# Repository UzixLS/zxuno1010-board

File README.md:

## ZX-UNO.1010
10x10cm PCB variant of ZX-Uno project

[[More photos]](images/README.md)

Tech specs:
- Fully compatible with ZX Uno v4.1 and ZX-Uno VGA 2M
- XC6SLX9 FPGA
- 2Mb SRAM memory
- VGA video output
- PAL/NTSC video + audio output via 3.5 jack connector (raspberry-pi compatible pinout)
- PS/2 keyboard and mouse ports
- 2xDB-9 ports for Atari-compatible joysticks
- SD/microSD card slot
- Tape input via Bluetooth module or ordinary 3.5 jack
- MIDI
- WiFi module
- RTC (starting from rev.B)
- Type C (starting from rev.D) or MicroUSB power supply
- Board optimized for G738 and G706 cases

FAQ on official site: [link](https://uto.speccy.org/zxunofaq_en.html)

Some random photos: [link](https://cloud.err200.net/index.php/s/73TR85tYZkMm8Ax?path=%2Fzxuno1010)

### Changelog
* Rev.A - first release ([main pcb errata](pcb/rev.A/ERRATA.txt) and [covers errata](pcb_covers/rev.A/ERRATA.txt)).
* Rev.A1 - fixes all known issues of rev.A.
* Rev.B:
    * added RTC
    * changed second joystick port wiring - in rev.A it's has been wired like in ZXUNO-VGA2M, but now it's wired like Joysplitter, which is officially supported way
    * joysticks are now powered by +5V rail instead of +3.3V - this should improve compatibility with various RF gamepads
    * optimized SAM2695 footprint for hand soldering
    * added opamp for proper MIDI sound mixing
    * added buffer in DAC circuit
    * added separate LDO for SD card and WiFi module
    * added resistor between WiFi's GPIO15 and GND to prevent IC heating
    * remove beeper (which wasn't used anyway)
    * improved power distribution for FPGA chip
    * pcb corners are rounded now
    * experimental tape-in circuit
* Rev.C:
    * added dedicated LDO for audio to improve noise floor
    * added optional capacitor for NTSC quartz stability
    * added missing decoupling capacitor on RTC power rail
    * added current-limiting resistors after opamp on sound output
    * changed R76, R80 from 10kΩ to 8.2kΩ
    * changed U10 opamp from NE5532 to LMV358 as it better suited for low-voltage operation
    * 3mm front leds replaced by 5mm
    * experimental reset circuit based on MAX809
    * reverted to old tape-in circuit
* Rev.D:
    * used USB Type C instead of Micro USB
    * PJ-320 3.5mm jack replaced by PJ-322
    * added solder jumper to select 3.5mm jack CVBS pinout
    * MIDI synthesizer U6 uses clean analog power rail now
    * improved W25Q128 footprint to able to install IC in WSON package
    * some minor PCB layout changes to reduce WiFi interference
    * reverted to old reset circuit
* Rev.D1:
    * changed R16 from 220Ω to 1kΩ to reduce power led bightness
    * changed R70, R71 from 10kΩ to 12kΩ to improve balance with AY
    * changed C51 from 100nF to 1uF to improve audio noise floor
    * changed C13 value as some quartz failed to start with 4.3pF load
    * changed U17 from LP2985-3.3 to TPS7A2033PDBVR due to better PSRR
    * changed U15 from 74LVC2G34 to 74LVC2G04 as it's more common in my projects

### References
* ZX Uno official site: [link](https://zxuno.speccy.org/index_e.shtml)
* ZX Uno VGA 2M: [link](https://github.com/ManuFerHi/ZXUNO_VGA_2M)
* Great collection of cores, games and much stuff for ZX Uno: [link](https://www.zxuno.com/forum/viewtopic.php?f=27&t=4142), [in english](https://www-zxuno-com.translate.goog/forum/viewtopic.php?f=27&t=4142&_x_tr_sl=es&_x_tr_tl=en)

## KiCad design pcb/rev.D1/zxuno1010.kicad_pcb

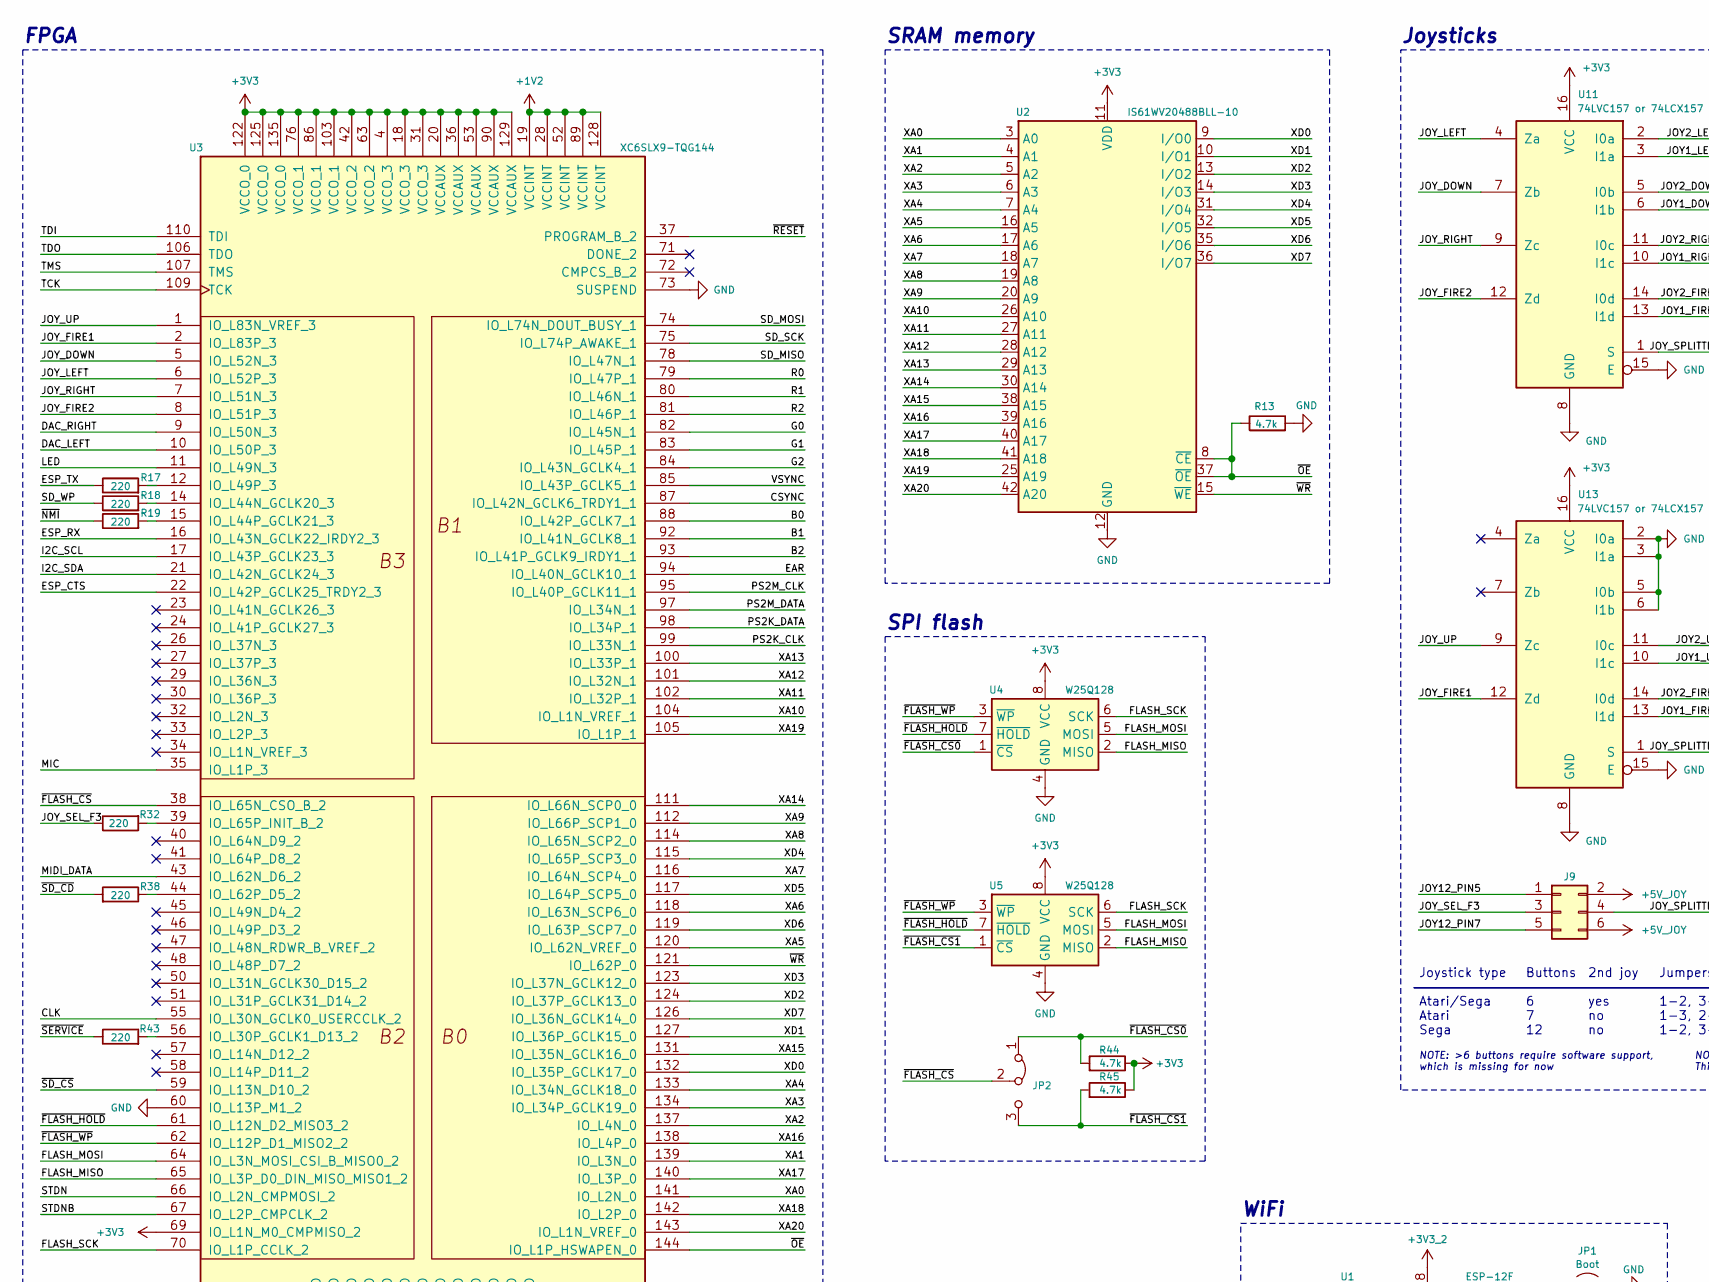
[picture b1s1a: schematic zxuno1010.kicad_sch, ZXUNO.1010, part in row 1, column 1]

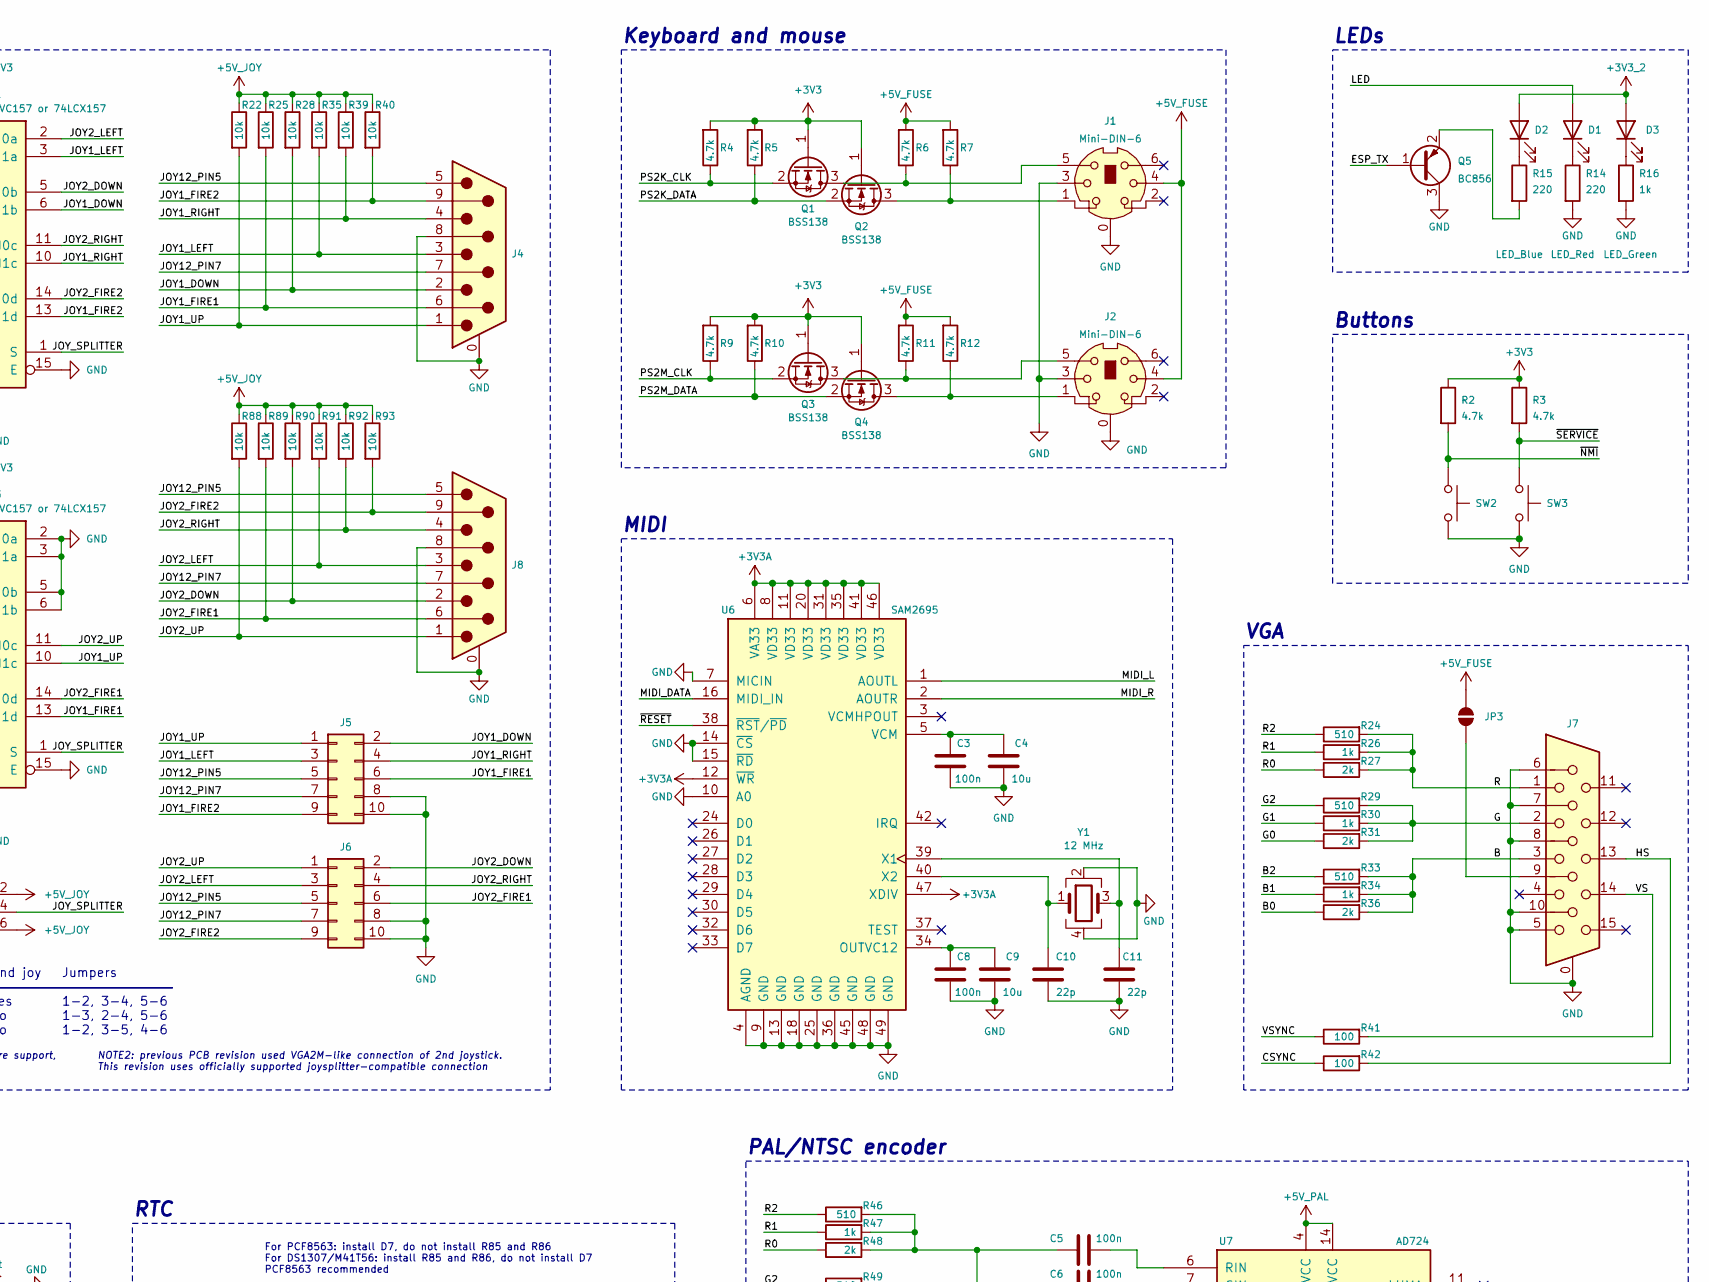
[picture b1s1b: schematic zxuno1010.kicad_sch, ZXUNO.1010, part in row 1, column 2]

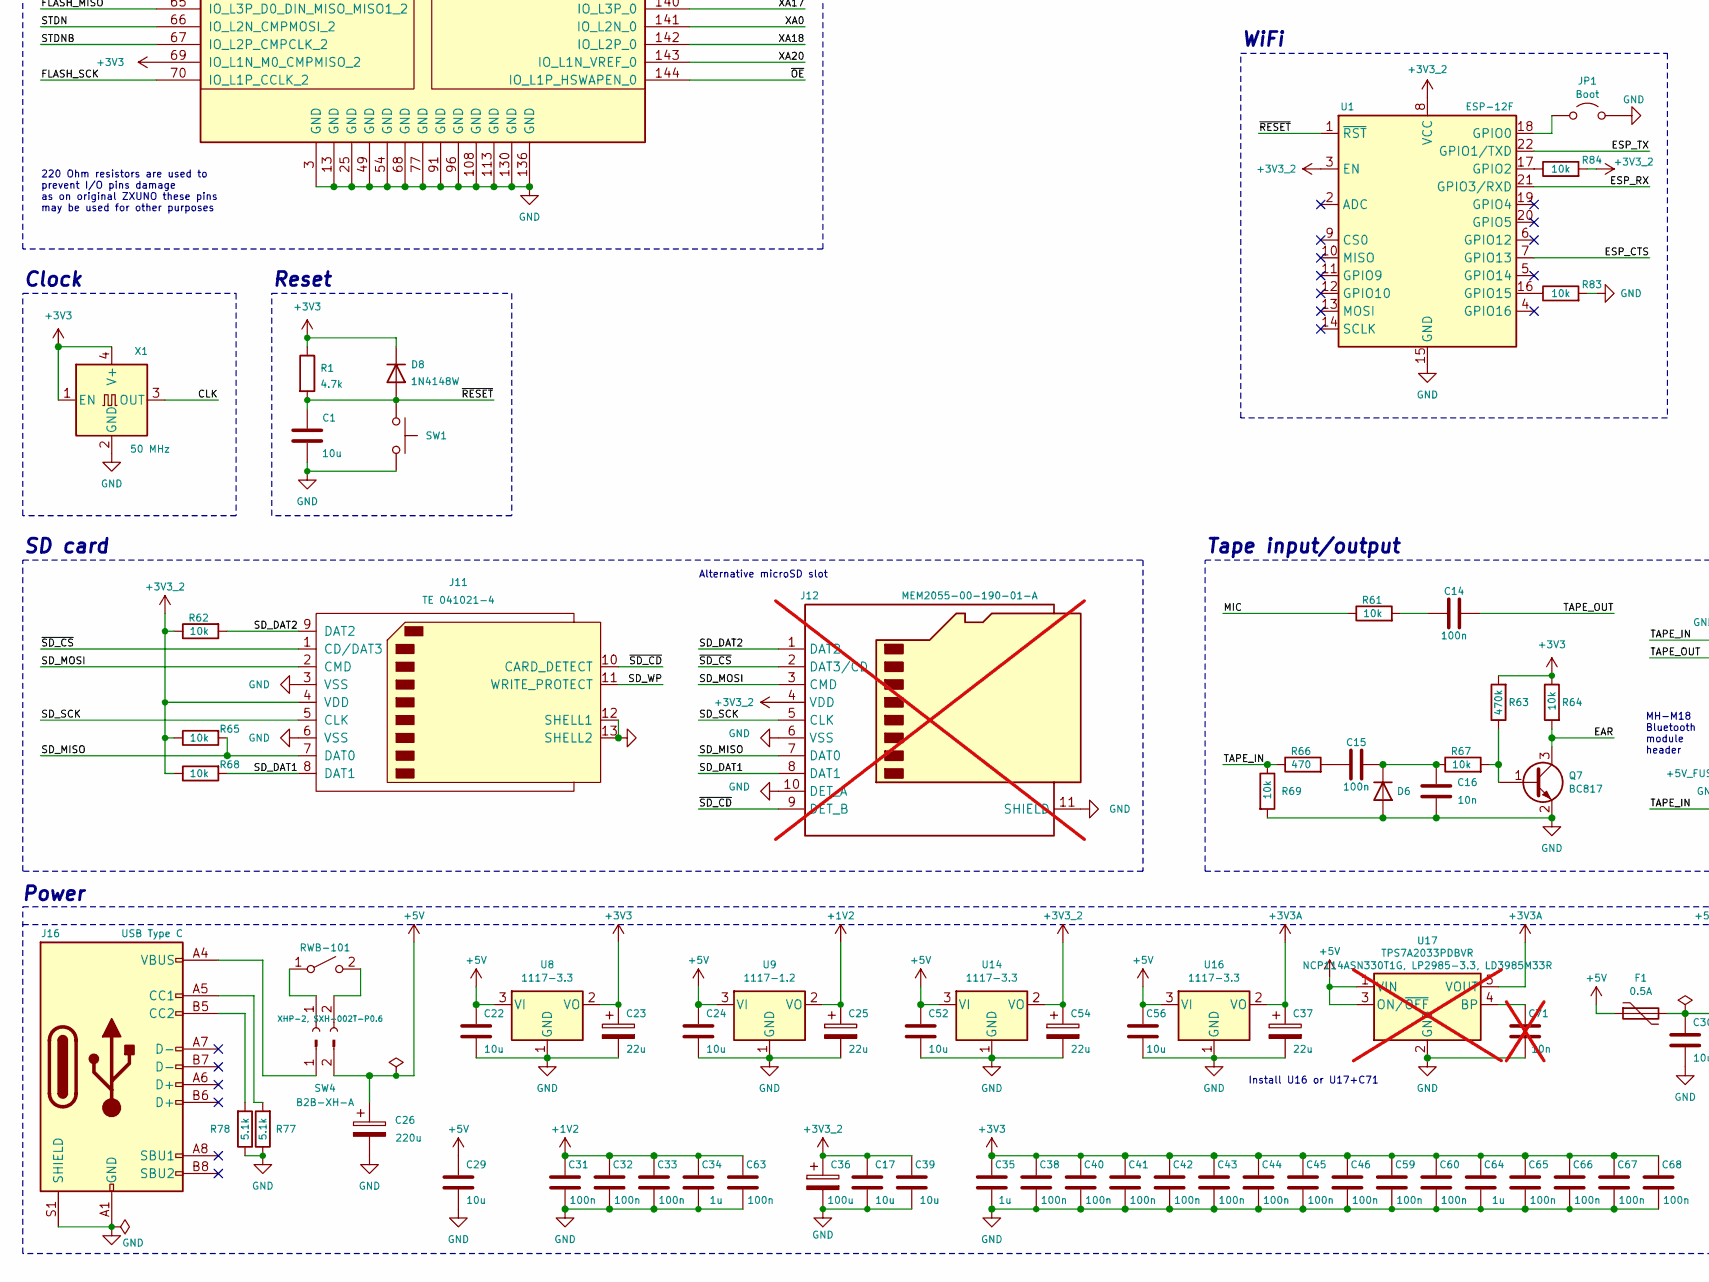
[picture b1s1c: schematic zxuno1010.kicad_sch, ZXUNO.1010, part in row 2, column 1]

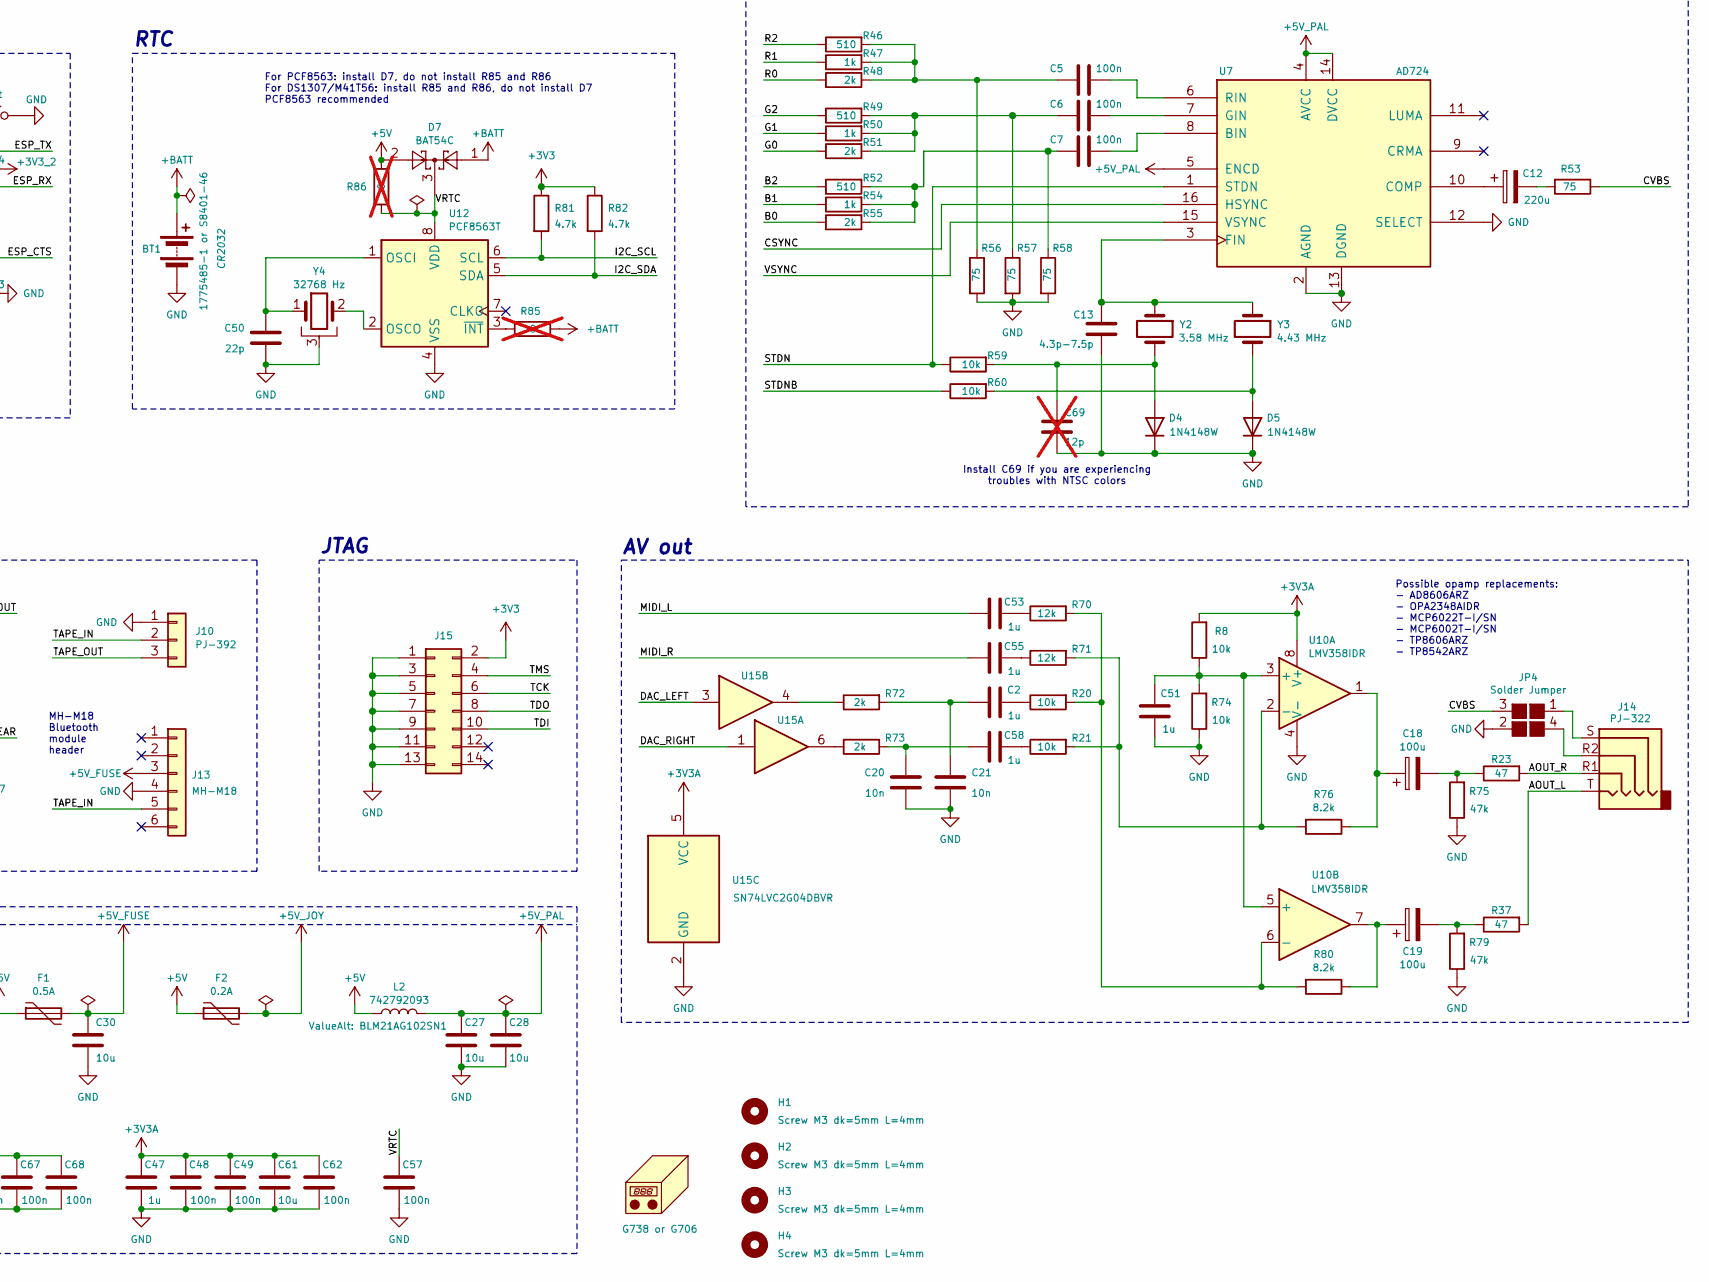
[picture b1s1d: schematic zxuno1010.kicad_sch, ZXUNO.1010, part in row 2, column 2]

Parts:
BT1: 1775485-1 or S8401-46; CR2032V
C1, C4, C9, C17, C22, C24, C27, C28, C29, C30, C39, C52, C56, C61: 10u; C_0805_2012Metric_Pad1.18x1.45mm_HandSolder
C2, C34, C35, C47, C51, C53, C55, C58, C64: 1u; C_0603_1608Metric_Pad1.08x0.95mm_HandSolder
C3, C5, C6, C7, C8, C14, C15, C31, C32, C33, C38, C40, C41, C42, C43, C44, C45, C46, C48, C49, C57, C59, C60, C62, C63, C65, C66, C67, C68: 100n; C_0603_1608Metric_Pad1.08x0.95mm_HandSolder
C10, C11, C50: 22p; C_0603_1608Metric_Pad1.08x0.95mm_HandSolder
C12, C26: 220u; CP_Elec_6.3x7.7
C13: 4.3p-7.5p; C_0603_1608Metric_Pad1.08x0.95mm_HandSolder
C16, C20, C21: 10n; C_0603_1608Metric_Pad1.08x0.95mm_HandSolder
C18, C19, C36: 100u; CP_Elec_5x5.9
C23, C25, C37, C54: 22u; CP_EIA-3216-18_Kemet-A_Pad1.58x1.35mm_HandSolder
C69: 12p; C_0603_1608Metric_Pad1.08x0.95mm_HandSolder; not fitted
C71: 10n; C_0603_1608Metric_Pad1.08x0.95mm_HandSolder; not fitted
D1: LED_Red; LED_D5.0mm_Horizontal_O1.27mm_Z3.0mm
D2: LED_Blue; LED_D5.0mm_Horizontal_O1.27mm_Z3.0mm
D3: LED_Green; LED_D5.0mm_Horizontal_O1.27mm_Z3.0mm
D4, D5, D6, D8: 1N4148W; D_SOD-123
D7: BAT54C; SOT-23
F1: 0.5A; Fuse_1812_4532Metric_Pad1.30x3.40mm_HandSolder
F2: 0.2A; Fuse_1812_4532Metric_Pad1.30x3.40mm_HandSolder
H1, H2, H3, H4: Screw M3 dk=5mm L=4mm; MountingHole_3.2mm_M3_dk5.2mm_Mask
J1, J2: Mini-DIN-6; minidin-6
J3: XHP-2, SXH-002T-P0.6
J4, J8: DB9-M; DSUB-9_Male_Horizontal_P2.77x2.84mm_EdgePinOffset4.94mm_Hou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
J5, J6: Conn_02x05_Odd_Even; PinHeader_2x05_P2.54mm_Vertical
J7: DB15_Female_HighDensity_MountingHoles; DSUB-15-HD_Female_Horizontal_P2.29x1.98mm_EdgePinOffset3.03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
J9: Conn_02x03_Odd_Even; PinHeader_2x03_P2.54mm_Vertical
J10: PJ-392; PinHeader_1x03_P2.54mm_Vertical
J11: TE 041021-4; SD_TE_2041021-mod
J12: MEM2055-00-190-01-A; GCT-MEM2055-00-190-01-A; not fitted
J13: MH-M18; PinHeader_1x06_P2.54mm_Vertical
J14: PJ-322
J15: Conn_02x07_Odd_Even; PinHeader_2x07_P2.54mm_Vertical
J16: USB Type C; USB_C_Receptacle_HRO_TYPE-C-31-M-12_dangling
JP1: Jumper; PinHeader_1x02_P2.54mm_Vertical
JP2: Jumper; PinHeader_1x03_P2.54mm_Vertical
JP3: SolderJumper_2_Open; SolderJumper-2_P1.3mm_Open_RoundedPad1.0x1.5mm
JP4: Solder Jumper; SolderJumper-4_P1.3mm_Open
L2: 742792093; L_0805_2012Metric_Pad1.15x1.40mm_HandSolder
N1: G738 or G706; g738-g706
Q1, Q2, Q3, Q4: BSS138; SOT-23
Q5: BC856; SOT-23
Q7: BC817; SOT-23
R1, R2, R3, R4, R5, R6, R7, R9, R10, R11, R12, R13, R44, R45, R81, R82: 4.7k; R_0603_1608Metric_Pad0.98x0.95mm_HandSolder
R8, R20, R21, R22, R25, R28, R35, R39, R40, R59, R60, R61, R62, R64, R65, R67, R68, R69, R74, R83, R84, R88, R89, R90, R91, R92, R93: 10k; R_0603_1608Metric_Pad0.98x0.95mm_HandSolder
R14, R15, R17, R18, R19, R32, R38, R43: 220; R_0603_1608Metric_Pad0.98x0.95mm_HandSolder
R16, R26, R30, R34, R47, R50, R54: 1k; R_0603_1608Metric_Pad0.98x0.95mm_HandSolder
R23, R37: 47; R_0603_1608Metric_Pad0.98x0.95mm_HandSolder
R24, R29, R33, R46, R49, R52: 510; R_0603_1608Metric_Pad0.98x0.95mm_HandSolder
R27, R31, R36, R48, R51, R55, R72, R73: 2k; R_0603_1608Metric_Pad0.98x0.95mm_HandSolder
R41, R42: 100; R_0603_1608Metric_Pad0.98x0.95mm_HandSolder
R53, R56, R57, R58: 75; R_0603_1608Metric_Pad0.98x0.95mm_HandSolder
R63: 470k; R_0603_1608Metric_Pad0.98x0.95mm_HandSolder
R66: 470; R_0603_1608Metric_Pad0.98x0.95mm_HandSolder
R70, R71: 12k; R_0603_1608Metric_Pad0.98x0.95mm_HandSolder
R75, R79: 47k; R_0603_1608Metric_Pad0.98x0.95mm_HandSolder
R76, R80: 8.2k; R_0603_1608Metric_Pad0.98x0.95mm_HandSolder
R77, R78: 5.1k; R_0603_1608Metric_Pad0.98x0.95mm_HandSolder
R85, R86: 0; R_0603_1608Metric_Pad0.98x0.95mm_HandSolder; not fitted
SW1, SW2, SW3: Push angle button, 6x6x7mm or 6x6x8mm; SW_Tactile_SPST_Angled_PTS645Vx58-2LFS
SW4: B2B-XH-A; JST_XH_B2B-XH-A_1x02_P2.50mm_Vertical
SW5: RWB-101
U1: ESP-12F; ESP-12E
U2: IS61WV20488BLL-10; TSOP-II-44_10.16x18.41mm_P0.8mm
U3: XC6SLX9-TQG144; LQFP-144_20x20mm_P0.5mm
U4, U5: W25Q128; SOIC-8_5.23x5.23mm_P1.27mm-LONG
U6: SAM2695; QFN-48-1EP_6x6mm_P0.4mm_EP4.2x4.2mm
U7: AD724; SOIC-16W_7.5x10.3mm_P1.27mm
U8, U14, U16: 1117-3.3; SOT-223-3_TabPin2
U9: 1117-1.2; SOT-223-3_TabPin2
U10: LMV358IDR; SOIC-8_3.9x4.9mm_P1.27mm
U11, U13: 74LVC157 or 74LCX157; TSSOP-16_4.4x5mm_P0.65mm
U12: PCF8563T; SOIC-8_3.9x4.9mm_P1.27mm
U15: SN74LVC2G04DBVR; SOT-23-6_Handsoldering
U17: TPS7A2033PDBVR; SOT-23-5_HandSoldering; not fitted
X1: 50 MHz; Oscillator_SMD_7050_7.0x5.0mm
Y1: 12 MHz; Crystal_SMD_SeikoEpson_TSX3225-4Pin_3.2x2.5mm_HandSoldering
Y2: 3.58 MHz; Crystal_HC49-4H_Vertical
Y3: 4.43 MHz; Crystal_HC49-4H_Vertical
Y4: 32768 Hz; Crystal_C38-LF_D3.0mm_L8.0mm_Horizontal_1EP_style2

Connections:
+1V2: C25.1, C31.2, C32.2, C33.2, C34.2, C63.2, U3.19 (VCCINT), U3.28 (VCCINT), U3.52 (VCCINT), U3.89 (VCCINT), U3.128 (VCCINT), U9.2 (VO)
+3V3: C23.1, C35.2, C38.2, C40.2, C41.2, C42.2, C43.2, C44.2, C45.2, C46.2, C59.2, C60.2, C64.2, C65.2, C66.2, C67.2, C68.2, D8.1 (K), J15.2, Q1.1 (G), Q2.1 (G), Q3.1 (G), Q4.1 (G), R1.1, R2.1, R3.1, R4.2, R5.2, R9.2, R10.2, R44.1, R45.1, R63.2, R64.1, R81.1, R82.1, U2.11 (VDD), U2.33 (VDD), U3.4 (VCCO_3), U3.18 (VCCO_3), U3.20 (VCCAUX), U3.31 (VCCO_3), U3.36 (VCCAUX), U3.42 (VCCO_2), U3.53 (VCCAUX), U3.63 (VCCO_2), U3.69 (IO_L1N_M0_CMPMISO_2), U3.76 (VCCO_1), U3.86 (VCCO_1), U3.90 (VCCAUX), U3.103 (VCCO_1), U3.122 (VCCO_0), U3.125 (VCCO_0), U3.129 (VCCAUX), U3.135 (VCCO_0), U4.8 (VCC), U5.8 (VCC), U8.2 (VO), U11.16 (VCC), U13.16 (VCC), X1.1 (EN), X1.4 (V+)
+3V3A: C37.1, C47.2, C48.2, C49.2, C61.2, C62.2, R8.2, U6.6 (VA33), U6.8 (VD33), U6.11 (VD33), U6.12 (~WR), U6.20 (VD33), U6.31 (VD33), U6.35 (VD33), U6.41 (VD33), U6.46 (VD33), U6.47 (XDIV), U10.8 (V+), U15.5 (VCC), U16.2 (VO), U17.5 (VOUT)
+3V3_2: C17.2, C36.1, C39.2, C54.1, D2.2 (A), D3.2 (A), J11.4 (VDD), J12.4 (VDD), R62.1, R65.1, R68.1, R84.2, U1.3 (EN), U1.8 (VCC), U14.2 (VO)
+5V: C22.2, C24.2, C26.1, C29.2, C52.2, C56.2, D7.2, F1.1, F2.1, L2.1, R86.2, SW4.2, U8.3 (VI), U9.3 (VI), U14.3 (VI), U16.3 (VI), U17.1 (VIN), U17.3 (ON/~OFF)
+5V_FUSE: C30.2, F1.2, J1.4, J2.4, J13.3, JP3.2 (B), R6.2, R7.2, R11.2, R12.2
+5V_JOY: F2.2, J9.2, J9.6, R22.1, R25.1, R28.1, R35.1, R39.1, R40.1, R88.1, R89.1, R90.1, R91.1, R92.1, R93.1
+5V_PAL: C27.2, C28.2, L2.2, U7.4 (AVCC), U7.5 (ENCD), U7.14 (DVCC)
+BATT: BT1.1 (+), D7.1, R85.2
/AOUT_L: J14.T, R37.2
/AOUT_R: J14.R1, R23.2
/B: J7.3, R33.2, R34.2, R36.2
/B0: R36.1, R55.1, U3.88 (IO_L42P_GCLK7_1)
/B1: R34.1, R54.1, U3.92 (IO_L41N_GCLK8_1)
/B2: R33.1, R52.1, U3.93 (IO_L41P_GCLK9_IRDY1_1)
/CLK: U3.55 (IO_L30N_GCLK0_USERCCLK_2), X1.3 (OUT)
/CSYNC: R42.1, U3.87 (IO_L42N_GCLK6_TRDY1_1), U7.16 (HSYNC)
/CVBS: JP4.3, R53.1
/DAC_LEFT: U3.10 (IO_L50P_3), U15.3
/DAC_RIGHT: U3.9 (IO_L50N_3), U15.1
/EAR: Q7.3 (C), R64.2, U3.94 (IO_L40N_GCLK10_1)
/ESP_CTS: U1.7 (GPIO13), U3.22 (IO_L42P_GCLK25_TRDY2_3)
/ESP_RX: U1.21 (GPIO3/RXD), U3.16 (IO_L43N_GCLK22_IRDY2_3)
/ESP_TX: Q5.1 (B), R17.1, U1.22 (GPIO1/TXD)
/FLASH_MISO: U3.65 (IO_L3P_D0_DIN_MISO_MISO1_2), U4.2 (MISO), U5.2 (MISO)
/FLASH_MOSI: U3.64 (IO_L3N_MOSI_CSI_B_MISO0_2), U4.5 (MOSI), U5.5 (MOSI)
/FLASH_SCK: U3.70 (IO_L1P_CCLK_2), U4.6 (SCK), U5.6 (SCK)
/G: J7.2, R29.2, R30.2, R31.2
/G0: R31.1, R51.1, U3.82 (IO_L45N_1)
/G1: R30.1, R50.1, U3.83 (IO_L45P_1)
/G2: R29.1, R49.1, U3.84 (IO_L43N_GCLK4_1)
/HS: J7.13, R42.2
/I2C_SCL: R81.2, U3.17 (IO_L43P_GCLK23_3), U12.6 (SCL)
/I2C_SDA: R82.2, U3.21 (IO_L42N_GCLK24_3), U12.5 (SDA)
/JOY1_DOWN: J4.2, J5.2, R28.2, U11.6 (I1b)
/JOY1_FIRE1: J4.6, J5.6, R25.2, U13.13 (I1d)
/JOY1_FIRE2: J4.9, J5.9, R40.2, U11.13 (I1d)
/JOY1_LEFT: J4.3, J5.3, R35.2, U11.3 (I1a)
/JOY1_RIGHT: J4.4, J5.4, R39.2, U11.10 (I1c)
/JOY1_UP: J4.1, J5.1, R22.2, U13.10 (I1c)
/JOY2_DOWN: J6.2, J8.2, R90.2, U11.5 (I0b)
/JOY2_FIRE1: J6.6, J8.6, R89.2, U13.14 (I0d)
/JOY2_FIRE2: J6.9, J8.9, R93.2, U11.14 (I0d)
/JOY2_LEFT: J6.3, J8.3, R91.2, U11.2 (I0a)
/JOY2_RIGHT: J6.4, J8.4, R92.2, U11.11 (I0c)
/JOY2_UP: J6.1, J8.1, R88.2, U13.11 (I0c)
/JOY12_PIN5: J4.5, J5.5, J6.5, J8.5, J9.1
/JOY12_PIN7: J4.7, J5.7, J6.7, J8.7, J9.5
/JOY_DOWN: U3.5 (IO_L52N_3), U11.7 (Zb)
/JOY_FIRE1: U3.2 (IO_L83P_3), U13.12 (Zd)
/JOY_FIRE2: U3.8 (IO_L51P_3), U11.12 (Zd)
/JOY_LEFT: U3.6 (IO_L52P_3), U11.4 (Za)
/JOY_RIGHT: U3.7 (IO_L51N_3), U11.9 (Zc)
/JOY_SEL_F3: J9.3, R32.1
/JOY_SPLITTER: J9.4, U11.1 (S), U13.1 (S)
/JOY_UP: U3.1 (IO_L83N_VREF_3), U13.9 (Zc)
/LED: D1.2 (A), U3.11 (IO_L49N_3)
/MIC: R61.1, U3.35 (IO_L1P_3)
/MIDI_DATA: U3.43 (IO_L62N_D6_2), U6.16 (MIDI_IN)
/MIDI_L: C53.1, U6.1 (AOUTL)
/MIDI_R: C55.1, U6.2 (AOUTR)
/PS2K_CLK: Q1.2 (S), R4.1, U3.99 (IO_L33N_1)
/PS2K_DATA: Q2.2 (S), R5.1, U3.98 (IO_L34P_1)
/PS2M_CLK: Q3.2 (S), R9.1, U3.95 (IO_L40P_GCLK11_1)
/PS2M_DATA: Q4.2 (S), R10.1, U3.97 (IO_L34N_1)
/R: J7.1, R24.2, R26.2, R27.2
/R0: R27.1, R48.1, U3.79 (IO_L47P_1)
/R1: R26.1, R47.1, U3.80 (IO_L46N_1)
/R2: R24.1, R46.1, U3.81 (IO_L46P_1)
/SD_DAT1: J11.8 (DAT1), J12.8 (DAT1), R68.2
/SD_DAT2: J11.9 (DAT2), J12.1 (DAT2), R62.2
/SD_MISO: J11.7 (DAT0), J12.7 (DAT0), R65.2, U3.78 (IO_L47N_1)
/SD_MOSI: J11.2 (CMD), J12.3 (CMD), U3.74 (IO_L74N_DOUT_BUSY_1)
/SD_SCK: J11.5 (CLK), J12.5 (CLK), U3.75 (IO_L74P_AWAKE_1)
/SD_WP: J11.11 (WRITE_PROTECT), R18.1
/STDN: R59.1, U3.66 (IO_L2N_CMPMOSI_2), U7.1 (STDN)
/STDNB: R60.1, U3.67 (IO_L2P_CMPCLK_2)
/TAPE_IN: J10.2, J13.5, R66.1, R69.1
/TAPE_OUT: C14.1, J10.3
/TCK: J15.6, U3.109 (TCK)
/TDI: J15.10, U3.110 (TDI)
/TDO: J15.8, U3.106 (TDO)
/TMS: J15.4, U3.107 (TMS)
/VRTC: C57.2, D7.3, R86.1, U12.8 (VDD)
/VS: J7.14, R41.2
/VSYNC: R41.1, U3.85 (IO_L43P_GCLK5_1), U7.15 (VSYNC)
/XA0: U2.3 (A0), U3.141 (IO_L2N_0)
/XA1: U2.4 (A1), U3.139 (IO_L3N_0)
/XA2: U2.5 (A2), U3.137 (IO_L4N_0)
/XA3: U2.6 (A3), U3.134 (IO_L34P_GCLK19_0)
/XA4: U2.7 (A4), U3.133 (IO_L34N_GCLK18_0)
/XA5: U2.16 (A5), U3.120 (IO_L62N_VREF_0)
/XA6: U2.17 (A6), U3.118 (IO_L63N_SCP6_0)
/XA7: U2.18 (A7), U3.116 (IO_L64N_SCP4_0)
/XA8: U2.19 (A8), U3.114 (IO_L65N_SCP2_0)
/XA9: U2.20 (A9), U3.112 (IO_L66P_SCP1_0)
/XA10: U2.26 (A10), U3.104 (IO_L1N_VREF_1)
/XA11: U2.27 (A11), U3.102 (IO_L32P_1)
/XA12: U2.28 (A12), U3.101 (IO_L32N_1)
/XA13: U2.29 (A13), U3.100 (IO_L33P_1)
/XA14: U2.30 (A14), U3.111 (IO_L66N_SCP0_0)
/XA15: U2.38 (A15), U3.131 (IO_L35N_GCLK16_0)
/XA16: U2.39 (A16), U3.138 (IO_L4P_0)
/XA17: U2.40 (A17), U3.140 (IO_L3P_0)
/XA18: U2.41 (A18), U3.142 (IO_L2P_0)
/XA19: U2.25 (A19), U3.105 (IO_L1P_1)
/XA20: U2.42 (A20), U3.143 (IO_L1N_VREF_0)
/XD0: U2.9 (I/O0), U3.132 (IO_L35P_GCLK17_0)
/XD1: U2.10 (I/O1), U3.127 (IO_L36P_GCLK15_0)
/XD2: U2.13 (I/O2), U3.124 (IO_L37P_GCLK13_0)
/XD3: U2.14 (I/O3), U3.123 (IO_L37N_GCLK12_0)
/XD4: U2.31 (I/O4), U3.115 (IO_L65P_SCP3_0)
/XD5: U2.32 (I/O5), U3.117 (IO_L64P_SCP5_0)
/XD6: U2.35 (I/O6), U3.119 (IO_L63P_SCP7_0)
/XD7: U2.36 (I/O7), U3.126 (IO_L36N_GCLK14_0)
/~FLASH_CS0: JP2.1 (A), R44.2, U4.1 (~CS)
/~FLASH_CS1: JP2.3 (B), R45.2, U5.1 (~CS)
/~FLASH_CS: JP2.2 (C), U3.38 (IO_L65N_CSO_B_2)
/~FLASH_HOLD: U3.61 (IO_L12N_D2_MISO3_2), U4.7 (~HOLD), U5.7 (~HOLD)
/~FLASH_WP: U3.62 (IO_L12P_D1_MISO2_2), U4.3 (~WP), U5.3 (~WP)
/~NMI: R2.2, R19.1, SW2.1
/~OE: R13.1, U2.8 (~CE), U2.37 (~OE), U3.144 (IO_L1P_HSWAPEN_0)
/~RESET: C1.2, D8.2 (A), R1.2, SW1.1, U1.1 (~RST), U3.37 (PROGRAM_B_2), U6.38 (~RST/~PD)
/~SD_CD: J11.10 (CARD_DETECT), J12.9 (DET_B), R38.2
/~SD_CS: J11.1 (CD/DAT3), J12.2 (DAT3/CD), U3.59 (IO_L13N_D10_2)
/~SERVICE: R3.2, R43.1, SW3.1
/~WR: U2.15 (~WE), U3.121 (IO_L62P_0)
GND: BT1.2 (-), C1.1, C3.1, C4.1, C8.1, C9.1, C10.1, C11.1, C13.2, C16.2, C17.1, C20.2, C21.2, C22.1, C23.2, C24.1, C25.2, C26.2, C27.1, C28.1, C29.1, C30.1, C31.1, C32.1, C33.1, C34.1, C35.1, C36.2, C37.2, C38.1, C39.1, C40.1, C41.1, C42.1, C43.1, C44.1, C45.1, C46.1, C47.1, C48.1, C49.1, C50.2, C51.1, C52.1, C54.2, C56.1, C57.1, C59.1, C60.1, C61.1, C62.1, C63.1, C64.1, C65.1, C66.1, C67.1, C68.1, C69.2, C71.1, D4.1 (K), D5.1 (K), D6.2 (A), J1.0, J1.3, J2.0, J2.3, J4.0 (PAD), J4.8, J5.8, J5.10, J6.8, J6.10, J7.0, J7.5, J7.6, J7.7, J7.8, J7.10, J8.0 (PAD), J8.8, J10.1, J11.3 (VSS), J11.6 (VSS), J11.12 (SHELL1), J11.13 (SHELL2), J12.6 (VSS), J12.10 (DET_A), J12.11 (SHIELD), J13.4, J15.1, J15.3, J15.5, J15.7, J15.9, J15.11, J15.13, J16.A1 (GND), J16.A12 (GND), J16.B1 (GND), J16.B12 (GND), J16.S1 (SHIELD), JP1.1 (A), JP4.2, Q5.3 (C), Q7.2 (E), R13.2, R14.2, R16.2, R56.2, R57.2, R58.2, R69.2, R74.1, R75.1, R77.1, R78.1, R79.1, R83.2, SW1.2, SW2.2, SW3.2, U1.15 (GND), U2.12 (GND), U2.34 (GND), U3.3 (GND), U3.13 (GND), U3.25 (GND), U3.49 (GND), U3.54 (GND), U3.60 (IO_L13P_M1_2), U3.68 (GND), U3.73 (SUSPEND), U3.77 (GND), U3.91 (GND), U3.96 (GND), U3.108 (GND), U3.113 (GND), U3.130 (GND), U3.136 (GND), U4.4 (GND), U5.4 (GND), U6.4 (AGND), U6.7 (MICIN), U6.9 (GND), U6.10 (A0), U6.13 (GND), U6.14 (~CS), U6.15 (~RD), U6.18 (GND), U6.25 (GND), U6.36 (GND), U6.45 (GND), U6.48 (GND), U6.49 (GND), U7.2 (AGND), U7.12 (SELECT), U7.13 (DGND), U8.1 (GND), U9.1 (GND), U10.4 (V-), U11.8 (GND), U11.15 (E), U12.4 (VSS), U13.2 (I0a), U13.3 (I1a), U13.5 (I0b), U13.6 (I1b), U13.8 (GND), U13.15 (E), U14.1 (GND), U15.2 (GND), U16.1 (GND), U17.2 (GND), X1.2 (GND), Y1.2, Y1.4, Y4.3
unnamed: C2.1, C21.1, R72.2
unnamed: C2.2, R20.1
unnamed: C5.2, R46.2, R47.2, R48.2, R56.1
unnamed: C6.2, R49.2, R50.2, R51.2, R57.1
unnamed: C7.2, R52.2, R54.2, R55.2, R58.1
unnamed: C12.2, R53.2
unnamed: C14.2, R61.2
unnamed: C15.2, R66.2
unnamed: C18.1, R76.1, U10.1
unnamed: C18.2, R23.1, R75.2
unnamed: C19.1, R80.1, U10.7
unnamed: C19.2, R37.1, R79.2
unnamed: C20.1, C58.1, R73.2
unnamed: C53.2, R70.1
unnamed: C55.2, R71.1
unnamed: C58.2, R21.1
unnamed: D1.1 (K), R14.1
unnamed: D2.1 (K), R15.1
unnamed: D3.1 (K), R16.1
unnamed: C69.1, D4.2 (A), R59.2, Y2.2
unnamed: D5.2 (A), R60.2, Y3.2
unnamed: C15.1, C16.1, D6.1 (K), R67.1
unnamed: J3.1, SW5.1 (A)
unnamed: J3.2, SW5.2 (B)
unnamed: J14.R2, JP4.4
unnamed: J16.A5 (CC1), R77.2
unnamed: J16.B5 (CC2), R78.2
unnamed: JP1.2 (B), U1.18 (GPIO0)
unnamed: J7.9, JP3.1 (A)
unnamed: J14.S, JP4.1 (A)
unnamed: J1.5, Q1.3 (D), R6.1
unnamed: J1.1, Q2.3 (D), R7.1
unnamed: J2.5, Q3.3 (D), R11.1
unnamed: J2.1, Q4.3 (D), R12.1
unnamed: Q5.2 (E), R15.2
unnamed: Q7.1 (B), R63.1, R67.2
unnamed: R72.1, U15.4
unnamed: R73.1, U15.6
unnamed: J16.A4 (VBUS), J16.A9 (VBUS), J16.B4 (VBUS), J16.B9 (VBUS), SW4.1
unnamed: R84.1, U1.17 (GPIO2)
unnamed: R83.1, U1.16 (GPIO15)
unnamed: R43.2, U3.56 (IO_L30P_GCLK1_D13_2)
unnamed: R18.2, U3.14 (IO_L44N_GCLK20_3)
unnamed: R19.2, U3.15 (IO_L44P_GCLK21_3)
unnamed: R17.2, U3.12 (IO_L49P_3)
unnamed: R38.1, U3.44 (IO_L62P_D5_2)
unnamed: R32.2, U3.39 (IO_L65P_INIT_B_2)
unnamed: C8.2, C9.2, U6.34 (OUTVC12)
unnamed: C3.2, C4.2, U6.5 (VCM)
unnamed: C11.2, U6.39 (X1), Y1.3
unnamed: C10.2, U6.40 (X2), Y1.1
unnamed: C7.1, U7.8 (BIN)
unnamed: C12.1, U7.10 (COMP)
unnamed: C13.1, U7.3 (FIN), Y2.1, Y3.1
unnamed: C6.1, U7.7 (GIN)
unnamed: C5.1, U7.6 (RIN)
unnamed: C51.2, R8.1, R74.2, U10.3 (+), U10.5 (+)
unnamed: R21.2, R71.2, R76.2, U10.2 (-)
unnamed: R20.2, R70.2, R80.2, U10.6 (-)
unnamed: C50.1, U12.1 (OSCI), Y4.1
unnamed: U12.2 (OSCO), Y4.2
unnamed: R85.1, U12.3 (~INT)
unnamed: C71.2, U17.4 (BP)

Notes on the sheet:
220 Ohm resistors are used to prevent I/O pins damage as on original ZXUNO these pins may be used for other purposes
Reset
Keyboard and mouse
Install C69 if you are experiencing troubles with NTSC colors
JTAG
For PCF8563: install D7, do not install R85 and R86 For DS1307/M41T56: install R85 and R86, do not install D7 PCF8563 recommended
Buttons
LEDs
MIDI
Jumpers 1-2, 3-4, 5-6 1-3, 2-4, 5-6 1-2, 3-5, 4-6
Install U16 or U17+C71
SD card
VGA
2nd joy yes no no
Clock
Tape input/output
NOTE: >6 buttons require software support, which is missing for now
NOTE2: previous PCB revision used VGA2M-like connection of 2nd joystick. This revision uses officially supported joysplitter-compatible connection
SRAM memory
AV out
Buttons 6 7 12
Possible opamp replacements: - AD8606ARZ - OPA2348AIDR - MCP6022T-I/SN - MCP6002T-I/SN - TP8606ARZ - TP8542ARZ
Joysticks
PAL/NTSC encoder
RTC
Alternative microSD slot
Joystick type Atari/Sega Atari Sega
Power
WiFi
FPGA
MH-M18 Bluetooth module header
SPI flash

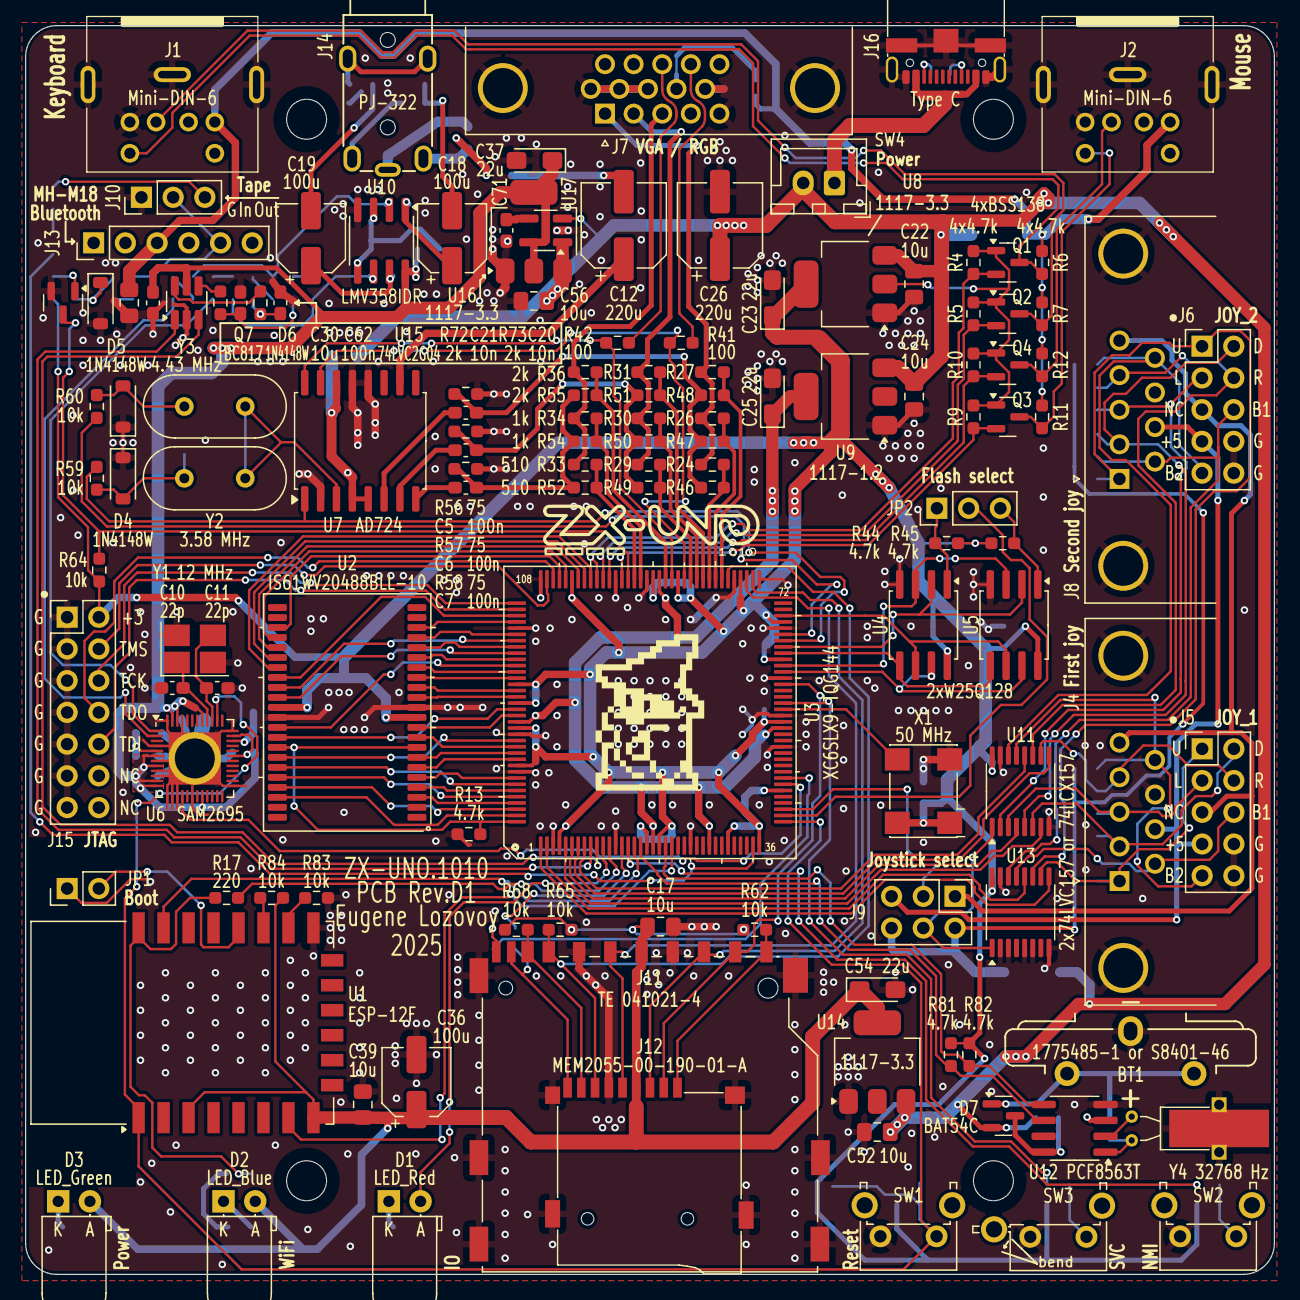
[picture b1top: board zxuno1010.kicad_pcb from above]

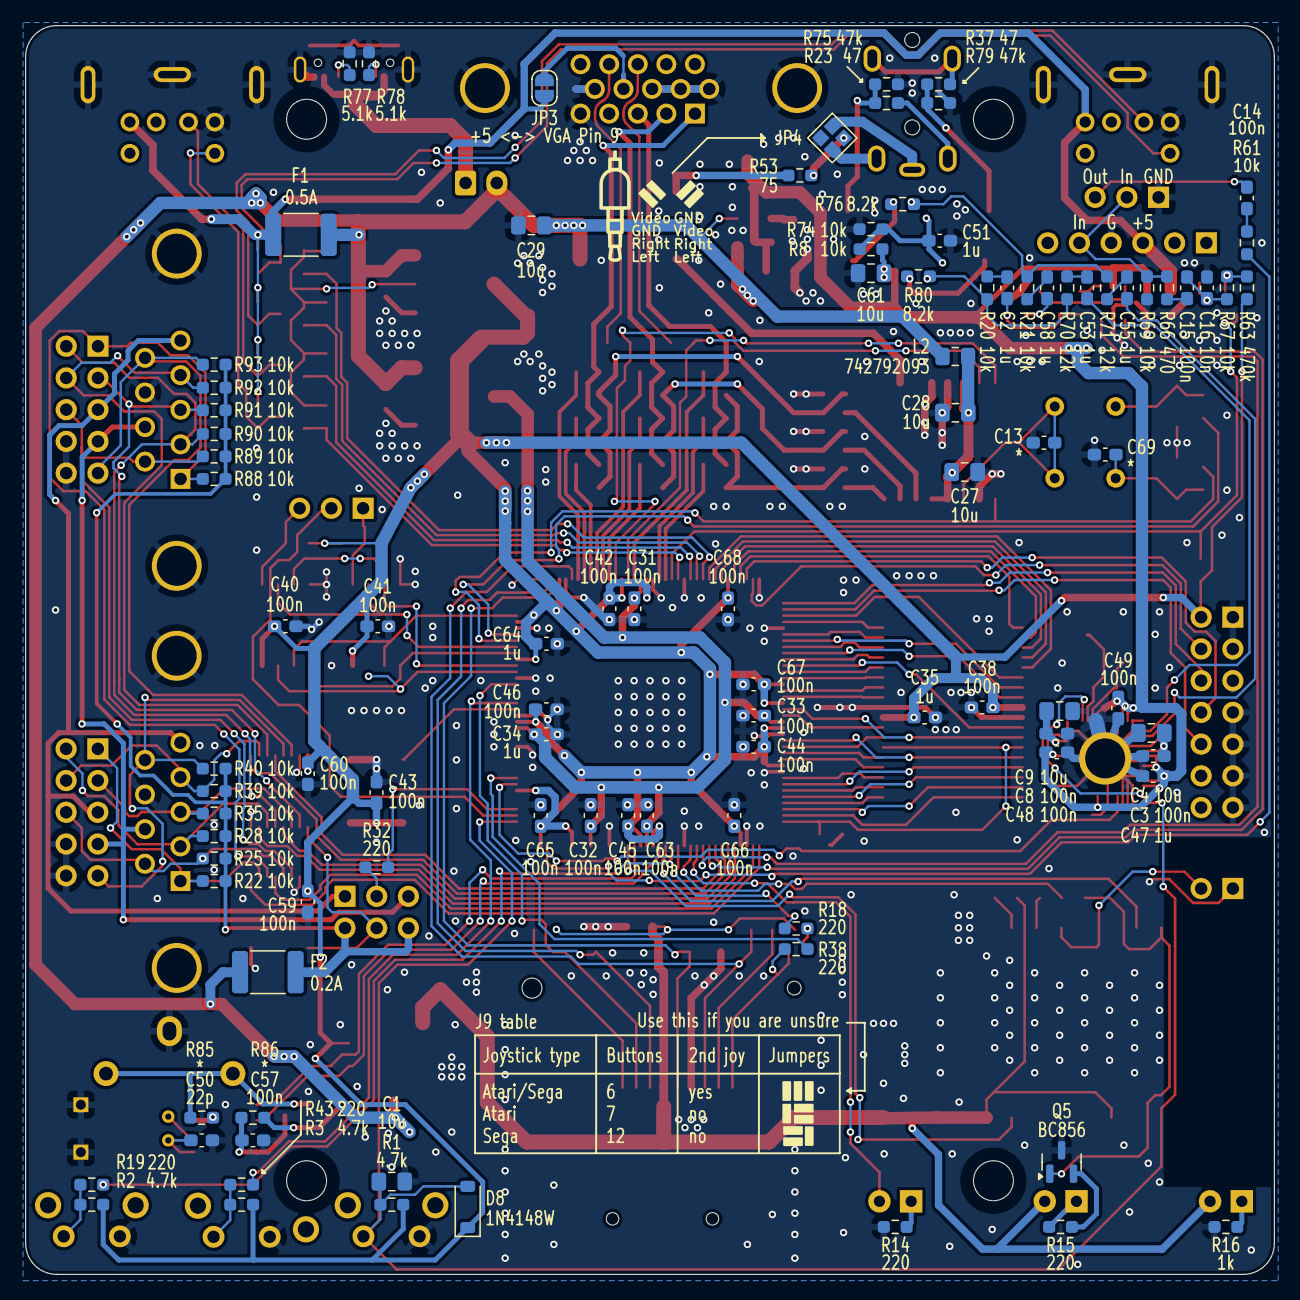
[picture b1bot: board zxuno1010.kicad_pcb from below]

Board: 2 copper layers, 100.0 x 100.0 mm, 232 parts (97 on the bottom side), 189 nets.

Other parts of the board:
LOGO1: graphic; zxuno_17x4.4
LOGO2: graphic; black-mage-12.5x8.6

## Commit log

2021-09-03 initial
2021-09-08 add readme
2021-11-12 add pcb covers rev.A
2021-12-27 add pcb rev.A1 gerber, pdf, etc...
2021-12-27 add pcb_covers rev.A1
2021-12-27 add flash.bin (taken from desUBIKado's distribution)
2021-12-27 add pcb rev.A1
2021-12-27 add errata
2022-05-26 add license
2022-05-26 update covers gerbers: fix "Lack of the Bottom Soldermask layer" for pcbway
2025-04-01 rename "out" -> "release"; merge 3d view into pdf
2025-04-19 add pcb rev.B
2025-04-19 add pcb rev.C
2025-04-19 add pcb rev.D
2025-04-19 add pcb rev D1 + release
2025-04-19 add new flash files
2025-04-19 update readme; add images gallery
2025-04-28 rev D1 pdf - add 3d renders
2025-05-02 add rev.A front photo
